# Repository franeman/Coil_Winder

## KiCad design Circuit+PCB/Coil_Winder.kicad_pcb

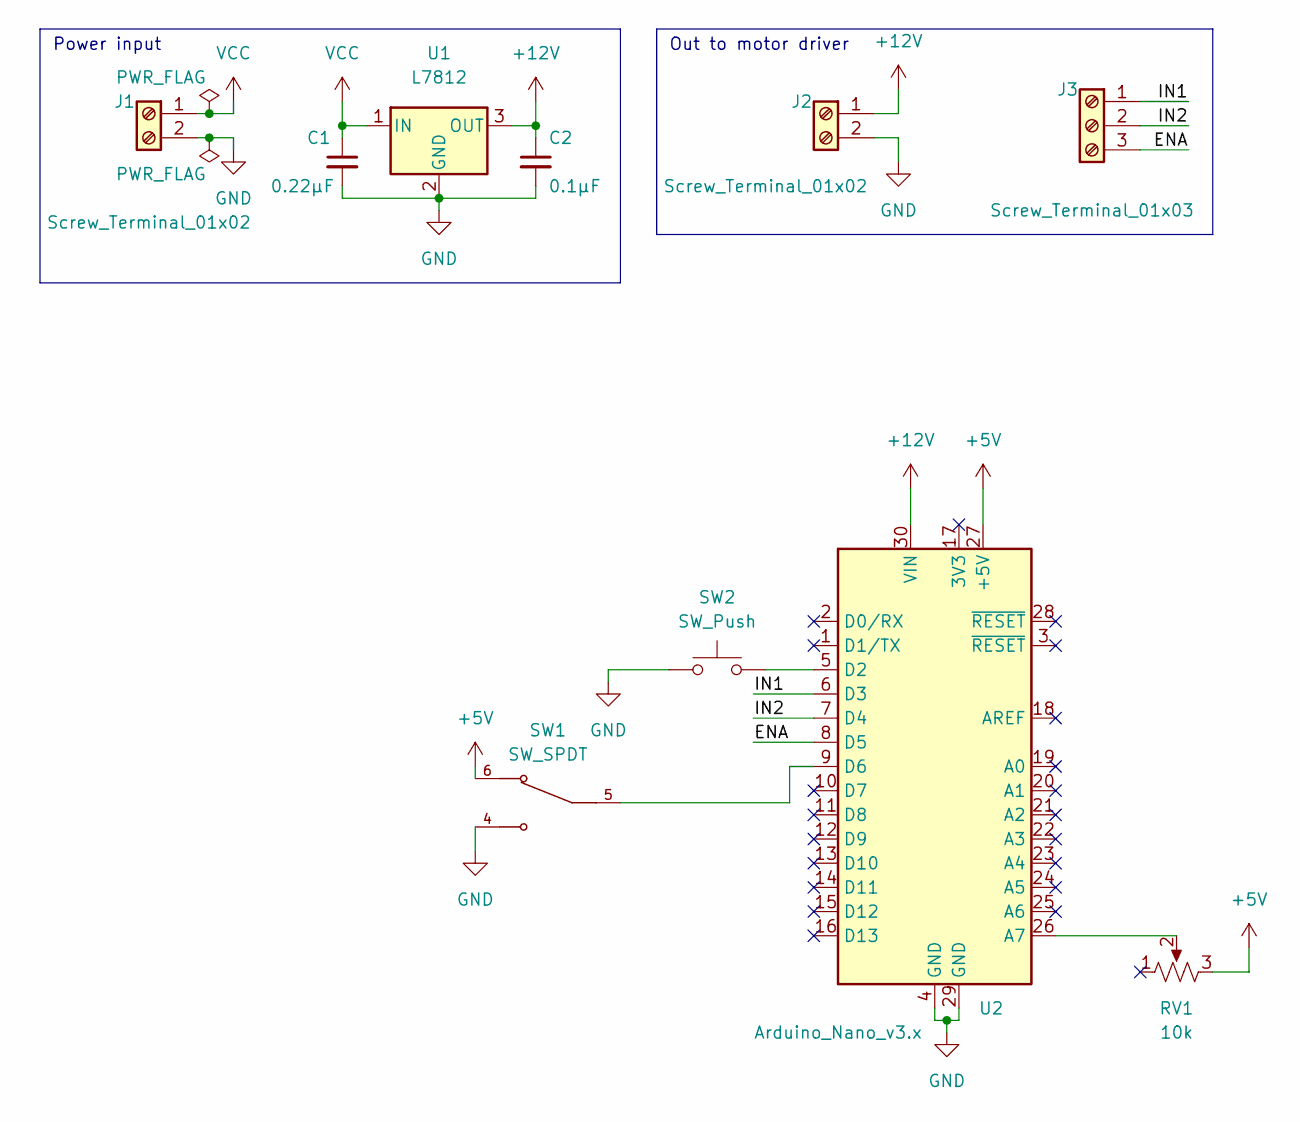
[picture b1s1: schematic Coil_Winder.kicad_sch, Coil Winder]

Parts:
C1: 0.22µF; C_Disc_D4.3mm_W1.9mm_P5.00mm
C2: 0.1µF; C_Disc_D4.3mm_W1.9mm_P5.00mm
J1, J2: Screw_Terminal_01x02; PinHeader_1x02_P2.54mm_Vertical
J3: Screw_Terminal_01x03; PinHeader_1x03_P2.54mm_Vertical
RV1: 10k; Potentiometer_Vishay_148-149_Single_Horizontal
SW1: SW_SPDT; SW_200USP1T1A1M6RE; PARTREV C
SW2: SW_Push; PinHeader_1x02_P2.54mm_Vertical
U1: L7812; TO-220-3_Vertical
U2: Arduino_Nano_v3.x; Arduino_Nano

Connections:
+5V: RV1.3, SW1.6, U2.27 (+5V)
+12V: C2.1, J2.1, U1.3 (OUT), U2.30 (VIN)
/ENA: J3.3, U2.8 (D5)
/IN1: J3.1, U2.6 (D3)
/IN2: J3.2, U2.7 (D4)
GND: C1.2, C2.2, J1.2, J2.2, SW1.4, SW2.1, U1.2 (GND), U2.4 (GND), U2.29 (GND)
unnamed: RV1.2, U2.26 (A7)
unnamed: SW1.5, U2.9 (D6)
unnamed: SW2.2, U2.5 (D2)
VCC: C1.1, J1.1, U1.1 (IN)

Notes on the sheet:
Power input
Out to motor driver

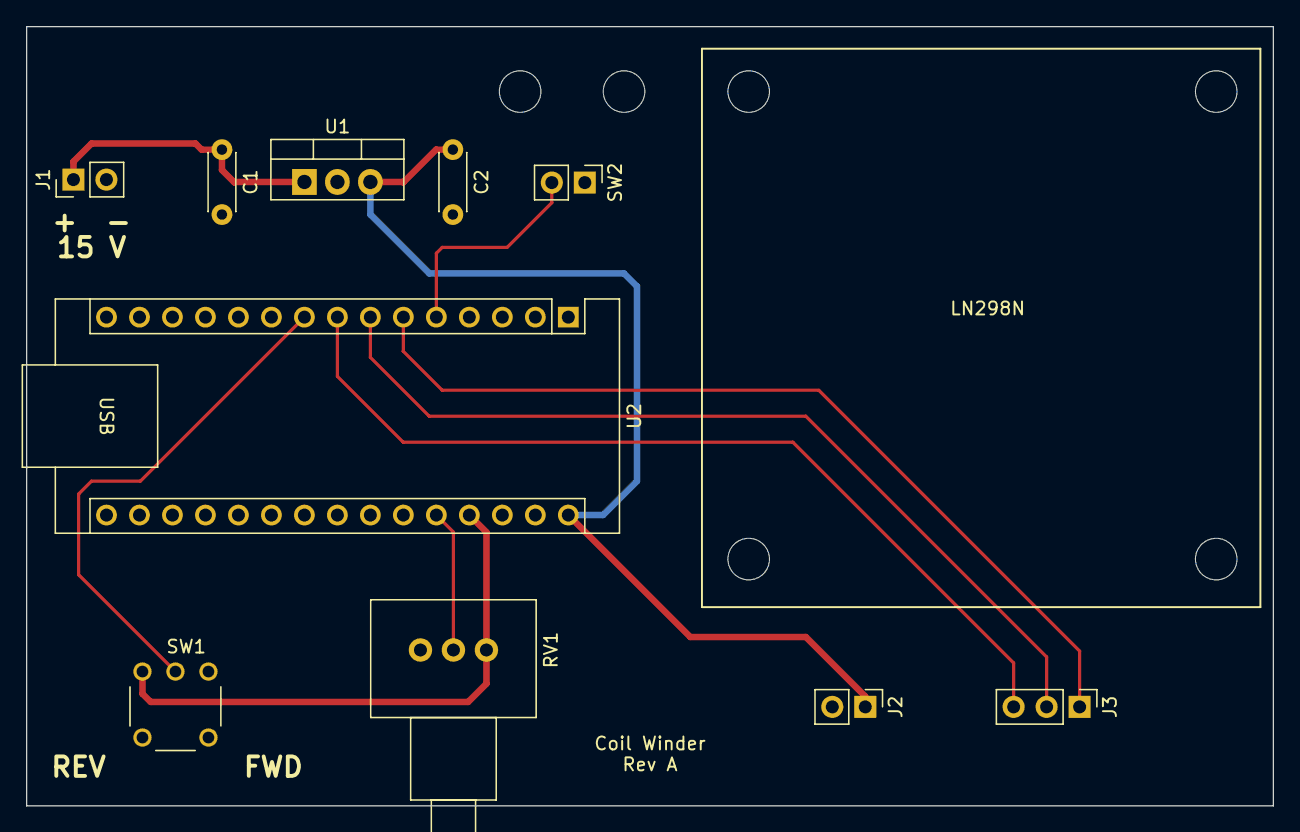
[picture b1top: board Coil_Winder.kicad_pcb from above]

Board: 2 copper layers, 96.0 x 60.0 mm, 10 parts (0 on the bottom side), 10 nets.

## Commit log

2023-02-09 Added shcematic and PCB files
2023-02-09 Generated BOM
